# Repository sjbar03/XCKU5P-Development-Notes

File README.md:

# XCKU5P Development Notes

A repository of all my notes as I learn PCB Design, Xilinx UltraScale+ FPGA, and Vivado.

Huge thanks to the creator of [this repository](https://github.com/tommythorn/AliExpressXCKU5P) for compiling all of the relevant technical info on this board!

Table of Contents
>    [1. VGA](./vga.md)
> 
>    [2. HDMI](./hdmi.md)
> 
>    [3. Protocols](./protocols.md)
> 
>    [4. PCB](./pcb.md)

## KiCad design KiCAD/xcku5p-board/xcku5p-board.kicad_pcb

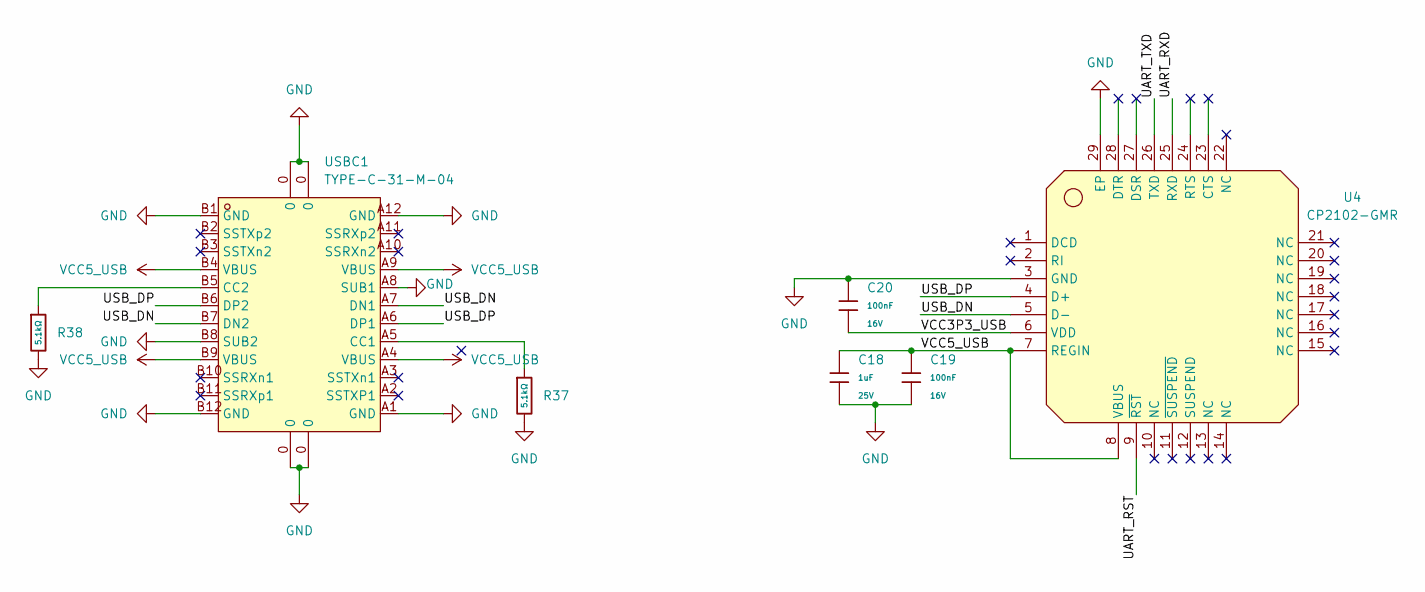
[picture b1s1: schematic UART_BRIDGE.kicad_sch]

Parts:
C18: 1uF; C_0402; Voltage Rated 25V; Tolerance ±10%; Part CL05A105KA5NQNC; LCSC C52923
C19, C20: 100nF; C_0402; Voltage Rated 16V; Tolerance ±10%; Part CL05B104KO5NNNC; LCSC C1525
R37, R38: 5.1kΩ; R_0402; Overload Voltage (Max) 50V; Tolerance ±1%; Part 0402WGF5101TCE; LCSC C25905
U4: CP2102-GMR; WQFN-28_L5.0-W5.0-P0.50-BL-EP3.2; LCSC Part C6568
USBC1: TYPE-C-31-M-04; USB-C-SMD_TYPE-C-USB-20; LCSC Part C129018

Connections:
/UART_BRIDGE/UART_RST: U4.9 (~RST)
/UART_BRIDGE/UART_RXD: U4.25 (RXD)
/UART_BRIDGE/UART_TXD: U4.26 (TXD)
/UART_BRIDGE/USB_DN: U4.5 (D-), USBC1.A7 (DN1), USBC1.B7 (DN2)
/UART_BRIDGE/USB_DP: U4.4 (D+), USBC1.A6 (DP1), USBC1.B6 (DP2)
/UART_BRIDGE/VCC3P3_USB: C20.2, U4.6 (VDD)
GND: C18.2, C19.2, C20.1, R37.2, R38.2, U4.3 (GND), U4.29 (EP), USBC1.0, USBC1.A1 (GND), USBC1.A8 (SUB1), USBC1.A12 (GND), USBC1.B1 (GND), USBC1.B8 (SUB2), USBC1.B12 (GND); also elsewhere on the board
unnamed: R37.1, USBC1.A5 (CC1)
unnamed: R38.1, USBC1.B5 (CC2)
VCC5_USB: C18.1, C19.1, U4.7 (REGIN), U4.8 (VBUS), USBC1.A4 (VBUS), USBC1.A9 (VBUS), USBC1.B4 (VBUS), USBC1.B9 (VBUS)

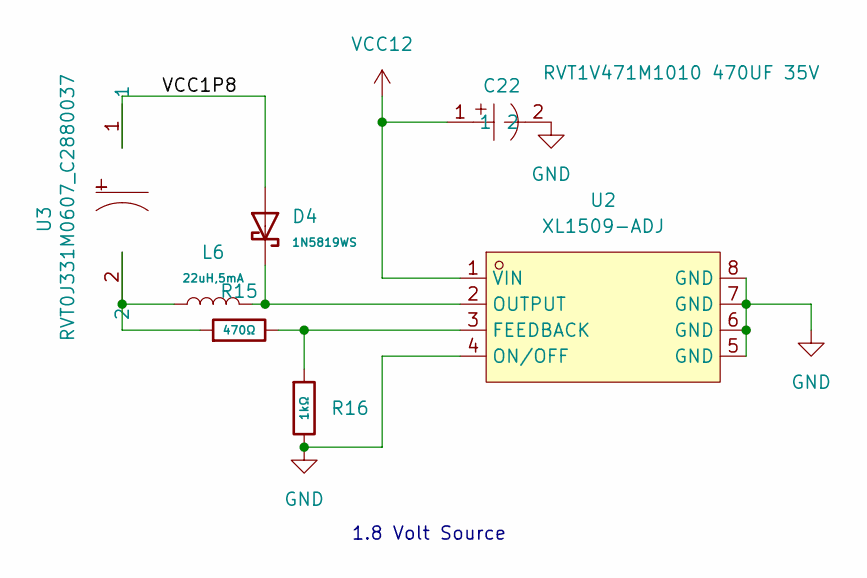
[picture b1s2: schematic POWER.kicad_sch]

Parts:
C22: RVT1V471M1010 470UF 35V; CAP-SMD_BD10.0-L10.3-W10.3-FD; LCSC Part C976030
D4: 1N5819WS; D_SOD-323; Forward Voltage (Vf@If) 600mV@1A; Reverse Voltage (Vr) 40V; Part 1N5819WS; LCSC C191023
L6: 22uH,5mA; L_0805; Tolerance ±10%; Part SDFL2012T220KTF; LCSC C32375
R15: 470Ω; R_0402; Overload Voltage (Max) 50V; Tolerance ±1%; Part 0402WGF4700TCE; LCSC C25117
R16: 1kΩ; R_0402; Overload Voltage (Max) 50V; Tolerance ±1%; Part 0402WGF1001TCE; LCSC C11702
U2: XL1509-ADJ; SOIC-8_L5.0-W4.0-P1.27-LS6.0-BL; LCSC Part C2681227
U3: RVT0J331M0607_C2880037; CAP-SMD_BD6.3-L6.6-W6.6-LS7.2-R-RD-1; LCSC Part C2880037

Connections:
/POWER/VCC1P8: D4.2, U3.1
GND: C22.2, R16.2, U2.4 (ON/OFF), U2.5 (GND), U2.6 (GND), U2.7 (GND), U2.8 (GND); also elsewhere on the board
unnamed: L6.1, R15.1, U3.2
unnamed: R15.2, R16.1, U2.3 (FEEDBACK)
unnamed: D4.1, L6.2, U2.2 (OUTPUT)
VCC12: C22.1, U2.1 (VIN)

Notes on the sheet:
1.8 Volt Source

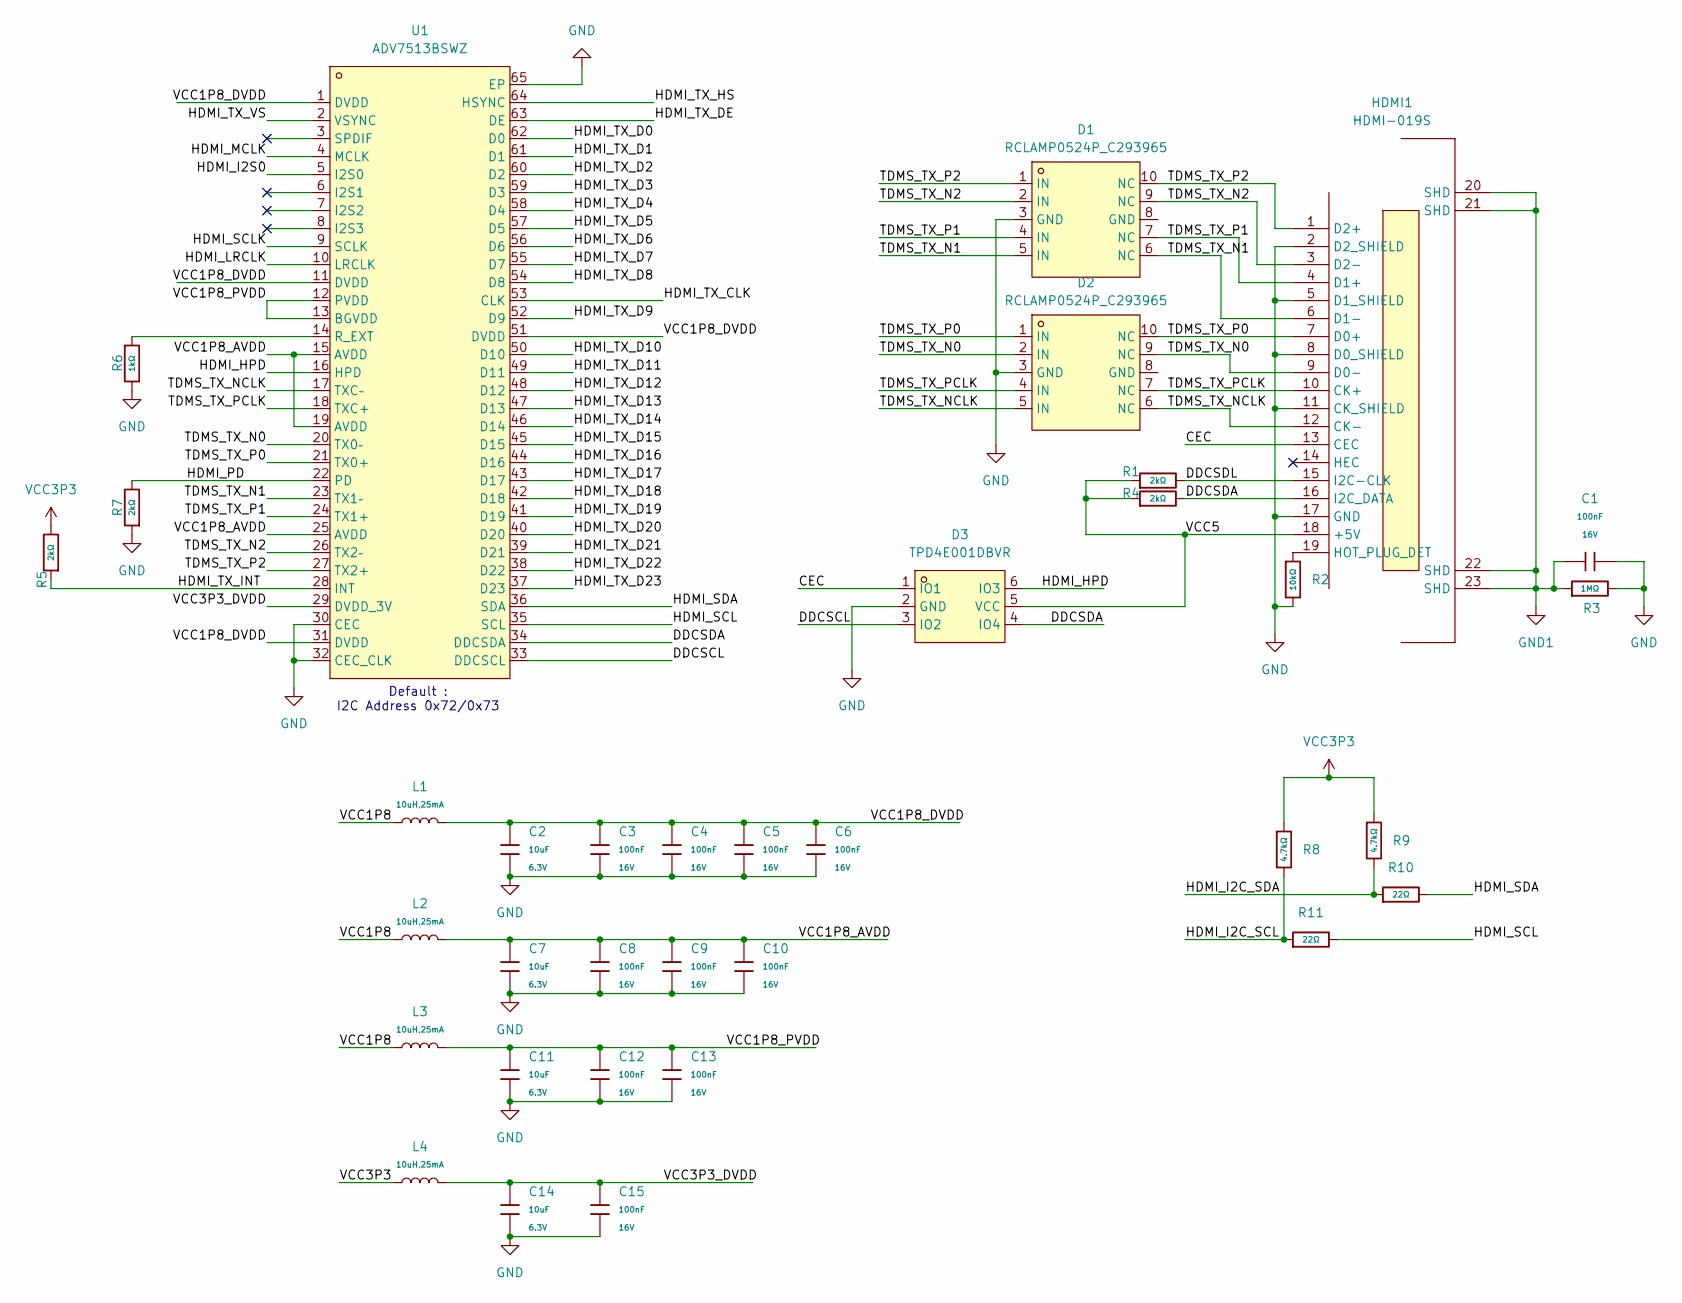
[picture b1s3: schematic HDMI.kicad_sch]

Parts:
C1, C3, C4, C5, C6, C8, C9, C10, C12, C13, C15: 100nF; C_0402; Voltage Rated 16V; Tolerance ±10%; Part CL05B104KO5NNNC; LCSC C1525
C2, C7, C11, C14: 10uF; C_0402; Voltage Rated 6.3V; Tolerance ±20%; Part CL05A106MQ5NUNC; LCSC C15525
D1, D2: RCLAMP0524P_C293965; DFN2510-10_L2.5-W1.0-P0.50-BL; LCSC Part C293965
D3: TPD4E001DBVR; SOT-23-6_L2.9-W1.6-P0.95-LS2.8-BL; LCSC Part C465736
HDMI1: HDMI-019S; HDMI-SMD_HDMI-019S; LCSC Part C111617
L1, L2, L3, L4: 10uH,25mA; L_1206; Tolerance ±10%; Part CMI321609X100KT; LCSC C1051
R1, R4, R5, R7: 2kΩ; R_0402; Overload Voltage (Max) 50V; Tolerance ±1%; Part 0402WGF2001TCE; LCSC C4109
R2: 10kΩ; R_0402; Overload Voltage (Max) 50V; Tolerance ±1%; Part 0402WGF1002TCE; LCSC C25744
R3: 1MΩ; R_0402; Overload Voltage (Max) 50V; Tolerance ±1%; Part 0402WGF1004TCE; LCSC C26083
R6: 1kΩ; R_0402; Overload Voltage (Max) 50V; Tolerance ±1%; Part 0402WGF1001TCE; LCSC C11702
R8, R9: 4.7kΩ; R_0402; Overload Voltage (Max) 50V; Tolerance ±1%; Part 0402WGF4701TCE; LCSC C25900
R10, R11: 22Ω; R_0402; Overload Voltage (Max) 50V; Tolerance ±1%; Part 0402WGF220JTCE; LCSC C25092
U1: ADV7513BSWZ; LQFP-64_L10.0-W10.0-P0.50-LS12.0-BL-EP5.3; LCSC Part C408901

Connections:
/HDMI/CEC: D3.1 (IO1), HDMI1.13 (CEC)
/HDMI/DDCSCL: D3.3 (IO2), U1.33 (DDCSCL)
/HDMI/DDCSDA: D3.4 (IO4), HDMI1.16 (I2C_DATA), R4.2, U1.34 (DDCSDA)
/HDMI/DDCSDL: HDMI1.15 (I2C-CLK), R1.2
/HDMI/HDMI_HPD: D3.6 (IO3), U1.16 (HPD)
/HDMI/HDMI_I2C_SCL: R8.2, R11.1
/HDMI/HDMI_I2C_SDA: R9.2, R10.1
/HDMI/HDMI_I2S0: U1.5 (I2S0)
/HDMI/HDMI_LRCLK: U1.10 (LRCLK)
/HDMI/HDMI_MCLK: U1.4 (MCLK)
/HDMI/HDMI_PD: R7.2, U1.22 (PD)
/HDMI/HDMI_SCL: R11.2, U1.35 (SCL)
/HDMI/HDMI_SCLK: U1.9 (SCLK)
/HDMI/HDMI_SDA: R10.2, U1.36 (SDA)
/HDMI/HDMI_TX_CLK: U1.53 (CLK)
/HDMI/HDMI_TX_D0: U1.62 (D0)
/HDMI/HDMI_TX_D1: U1.61 (D1)
/HDMI/HDMI_TX_D2: U1.60 (D2)
/HDMI/HDMI_TX_D3: U1.59 (D3)
/HDMI/HDMI_TX_D4: U1.58 (D4)
/HDMI/HDMI_TX_D5: U1.57 (D5)
/HDMI/HDMI_TX_D6: U1.56 (D6)
/HDMI/HDMI_TX_D7: U1.55 (D7)
/HDMI/HDMI_TX_D8: U1.54 (D8)
/HDMI/HDMI_TX_D9: U1.52 (D9)
/HDMI/HDMI_TX_D10: U1.50 (D10)
/HDMI/HDMI_TX_D11: U1.49 (D11)
/HDMI/HDMI_TX_D12: U1.48 (D12)
/HDMI/HDMI_TX_D13: U1.47 (D13)
/HDMI/HDMI_TX_D14: U1.46 (D14)
/HDMI/HDMI_TX_D15: U1.45 (D15)
/HDMI/HDMI_TX_D16: U1.44 (D16)
/HDMI/HDMI_TX_D17: U1.43 (D17)
/HDMI/HDMI_TX_D18: U1.42 (D18)
/HDMI/HDMI_TX_D19: U1.41 (D19)
/HDMI/HDMI_TX_D20: U1.40 (D20)
/HDMI/HDMI_TX_D21: U1.39 (D21)
/HDMI/HDMI_TX_D22: U1.38 (D22)
/HDMI/HDMI_TX_D23: U1.37 (D23)
/HDMI/HDMI_TX_DE: U1.63 (DE)
/HDMI/HDMI_TX_HS: U1.64 (HSYNC)
/HDMI/HDMI_TX_INT: R5.1, U1.28 (INT)
/HDMI/HDMI_TX_VS: U1.2 (VSYNC)
/HDMI/TDMS_TX_N0: D2.2 (IN), D2.9 (NC), HDMI1.9 (D0-), U1.20 (TX0–)
/HDMI/TDMS_TX_N1: D1.5 (IN), D1.6 (NC), HDMI1.6 (D1-), U1.23 (TX1–)
/HDMI/TDMS_TX_N2: D1.2 (IN), D1.9 (NC), HDMI1.3 (D2-), U1.26 (TX2–)
/HDMI/TDMS_TX_NCLK: D2.5 (IN), D2.6 (NC), HDMI1.12 (CK-), U1.17 (TXC–)
/HDMI/TDMS_TX_P0: D2.1 (IN), D2.10 (NC), HDMI1.7 (D0+), U1.21 (TX0+)
/HDMI/TDMS_TX_P1: D1.4 (IN), D1.7 (NC), HDMI1.4 (D1+), U1.24 (TX1+)
/HDMI/TDMS_TX_P2: D1.1 (IN), D1.10 (NC), HDMI1.1 (D2+), U1.27 (TX2+)
/HDMI/TDMS_TX_PCLK: D2.4 (IN), D2.7 (NC), HDMI1.10 (CK+), U1.18 (TXC+)
/HDMI/VCC1P8: L1.1, L2.1, L3.1
/HDMI/VCC1P8_AVDD: C7.1, C8.2, C9.2, C10.2, L2.2, U1.15 (AVDD), U1.19 (AVDD), U1.25 (AVDD)
/HDMI/VCC1P8_DVDD: C2.1, C3.2, C4.2, C5.2, C6.2, L1.2, U1.1 (DVDD), U1.11 (DVDD), U1.31 (DVDD), U1.51 (DVDD)
/HDMI/VCC1P8_PVDD: C11.1, C12.2, C13.2, L3.2, U1.12 (PVDD), U1.13 (BGVDD)
/HDMI/VCC3P3_DVDD: C14.1, C15.2, L4.2, U1.29 (DVDD_3V)
/HDMI/VCC5: D3.5 (VCC), HDMI1.18 (+5V), R1.1, R4.1
GND: C1.2, C2.2, C3.1, C4.1, C5.1, C6.1, C7.2, C8.1, C9.1, C10.1, C11.2, C12.1, C13.1, C14.2, C15.1, D1.3 (GND), D2.3 (GND), D3.2 (GND), HDMI1.2 (D2_SHIELD), HDMI1.5 (D1_SHIELD), HDMI1.8 (D0_SHIELD), HDMI1.11 (CK_SHIELD), HDMI1.17 (GND), R2.2, R3.2, R6.2, R7.1, U1.30 (CEC), U1.32 (CEC_CLK), U1.65 (EP); also elsewhere on the board
GND1: C1.1, HDMI1.20 (SHD), HDMI1.21 (SHD), HDMI1.22 (SHD), HDMI1.23 (SHD), R3.1
unnamed: HDMI1.19 (HOT_PLUG_DET), R2.1
unnamed: R6.1, U1.14 (R_EXT)
VCC3P3: L4.1, R5.2, R8.1, R9.1; also elsewhere on the board

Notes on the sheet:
Default : I2C Address 0x72/0x73

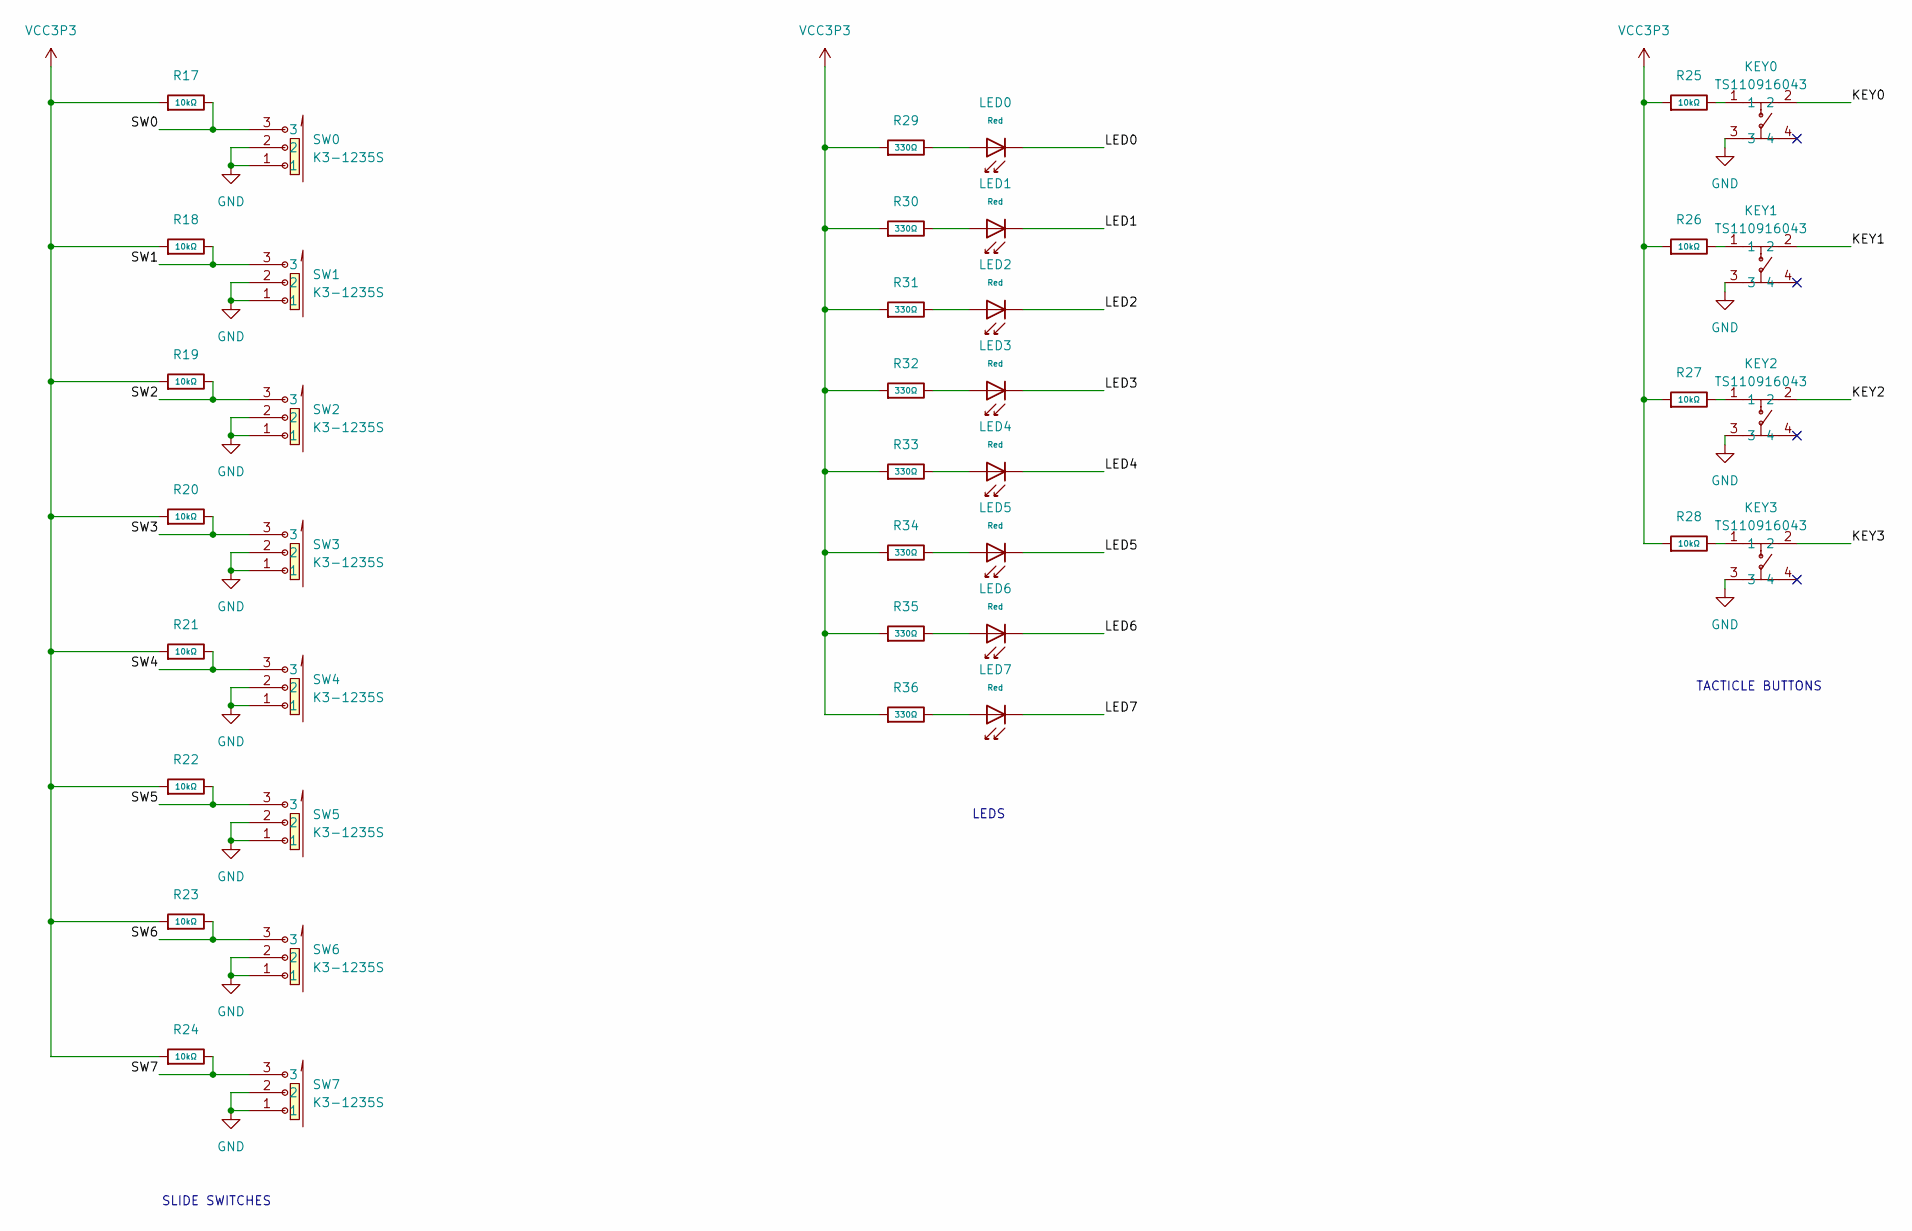
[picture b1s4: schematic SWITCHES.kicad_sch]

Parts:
KEY0, KEY1, KEY2, KEY3: TS110916043; SW-SMD_4P-L4.5-W4.5-P3.00-LS7.5; LCSC Part C22375348
LED0, LED1, LED2, LED3, LED4, LED5, LED6, LED7: Red; D_0603; Part KT-0603R; LCSC C2286
R17, R18, R19, R20, R21, R22, R23, R24, R25, R26, R27, R28: 10kΩ; R_0402; Overload Voltage (Max) 50V; Tolerance ±1%; Part 0402WGF1002TCE; LCSC C25744
R29, R30, R31, R32, R33, R34, R35, R36: 330Ω; R_0402; Overload Voltage (Max) 50V; Tolerance ±1%; Part 0402WGF3300TCE; LCSC C25104
SW0, SW1, SW2, SW3, SW4, SW5, SW6, SW7: K3-1235S; SW-SMD_K3-1235S-K1; LCSC Part C92660

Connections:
/SWITCHES/KEY0: KEY0.2
/SWITCHES/KEY1: KEY1.2
/SWITCHES/KEY2: KEY2.2
/SWITCHES/KEY3: KEY3.2
/SWITCHES/LED0: LED0.1
/SWITCHES/LED1: LED1.1
/SWITCHES/LED2: LED2.1
/SWITCHES/LED3: LED3.1
/SWITCHES/LED4: LED4.1
/SWITCHES/LED5: LED5.1
/SWITCHES/LED6: LED6.1
/SWITCHES/LED7: LED7.1
/SWITCHES/SW0: R17.2, SW0.3
/SWITCHES/SW1: R18.2, SW1.3
/SWITCHES/SW2: R19.2, SW2.3
/SWITCHES/SW3: R20.2, SW3.3
/SWITCHES/SW4: R21.2, SW4.3
/SWITCHES/SW5: R22.2, SW5.3
/SWITCHES/SW6: R23.2, SW6.3
/SWITCHES/SW7: R24.2, SW7.3
GND: KEY0.3, KEY1.3, KEY2.3, KEY3.3, SW0.1, SW0.2, SW1.1, SW1.2, SW2.1, SW2.2, SW3.1, SW3.2, SW4.1, SW4.2, SW5.1, SW5.2, SW6.1, SW6.2, SW7.1, SW7.2; also elsewhere on the board
unnamed: KEY0.1, R25.2
unnamed: KEY1.1, R26.2
unnamed: KEY2.1, R27.2
unnamed: KEY3.1, R28.2
unnamed: LED0.2, R29.2
unnamed: LED1.2, R30.2
unnamed: LED2.2, R31.2
unnamed: LED3.2, R32.2
unnamed: LED4.2, R33.2
unnamed: LED5.2, R34.2
unnamed: LED6.2, R35.2
unnamed: LED7.2, R36.2
VCC3P3: R17.1, R18.1, R19.1, R20.1, R21.1, R22.1, R23.1, R24.1, R25.1, R26.1, R27.1, R28.1, R29.1, R30.1, R31.1, R32.1, R33.1, R34.1, R35.1, R36.1; also elsewhere on the board

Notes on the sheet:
LEDS
TACTICLE BUTTONS
SLIDE SWITCHES

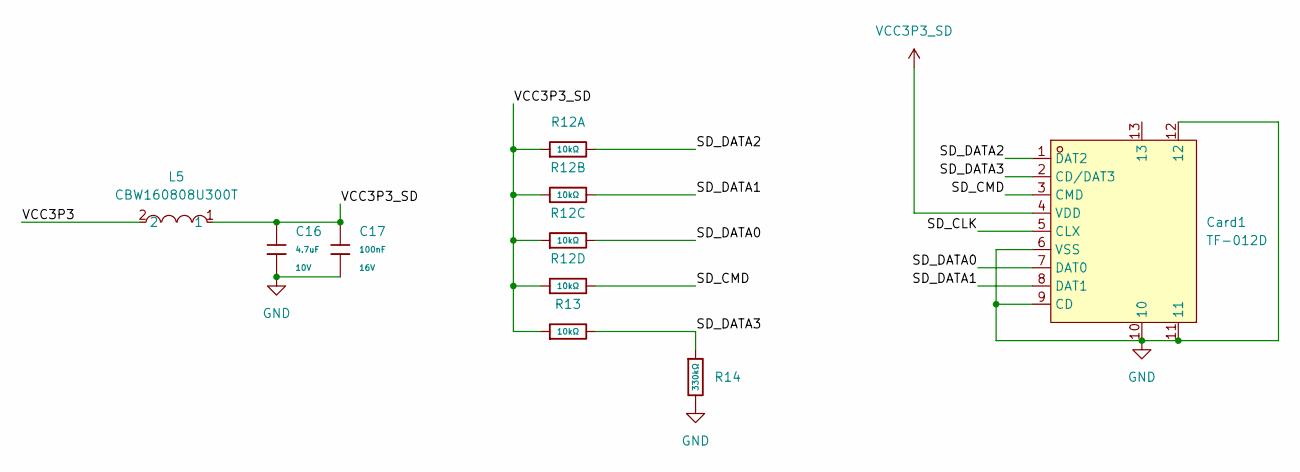
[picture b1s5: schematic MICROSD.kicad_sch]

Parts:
C16: 4.7uF; C_0402; Voltage Rated 10V; Tolerance ±20%; Part CL05A475MP5NRNC; LCSC C23733
C17: 100nF; C_0402; Voltage Rated 16V; Tolerance ±10%; Part CL05B104KO5NNNC; LCSC C1525
Card1: TF-012D; TF-SMD_TF-012; LCSC Part C2874207
L5: CBW160808U300T; L0603; LCSC Part C139178
R12: 10kΩ; R_0402x4; Tolerance ±5%; Part 4D02WGJ0103TCE; LCSC C25725
R13: 10kΩ; R_0402; Overload Voltage (Max) 50V; Tolerance ±1%; Part 0402WGF1002TCE; LCSC C25744
R14: 330kΩ; R_0402; Overload Voltage (Max) 50V; Tolerance ±1%; Part 0402WGF3303TCE; LCSC C25778

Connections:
/MICROSD/SD_CLK: Card1.5 (CLX)
/MICROSD/SD_CMD: Card1.3 (CMD), R12.5
/MICROSD/SD_DATA0: Card1.7 (DAT0), R12.6
/MICROSD/SD_DATA1: Card1.8 (DAT1), R12.7
/MICROSD/SD_DATA2: Card1.1 (DAT2), R12.8
/MICROSD/SD_DATA3: Card1.2 (CD/DAT3), R13.2, R14.1
/MICROSD/VCC3P3: L5.2
GND: C16.2, C17.2, Card1.6 (VSS), Card1.9 (CD), Card1.10, Card1.11, Card1.12, R14.2; also elsewhere on the board
VCC3P3_SD: C16.1, C17.1, Card1.4 (VDD), L5.1, R12.1, R12.2, R12.3, R12.4, R13.1

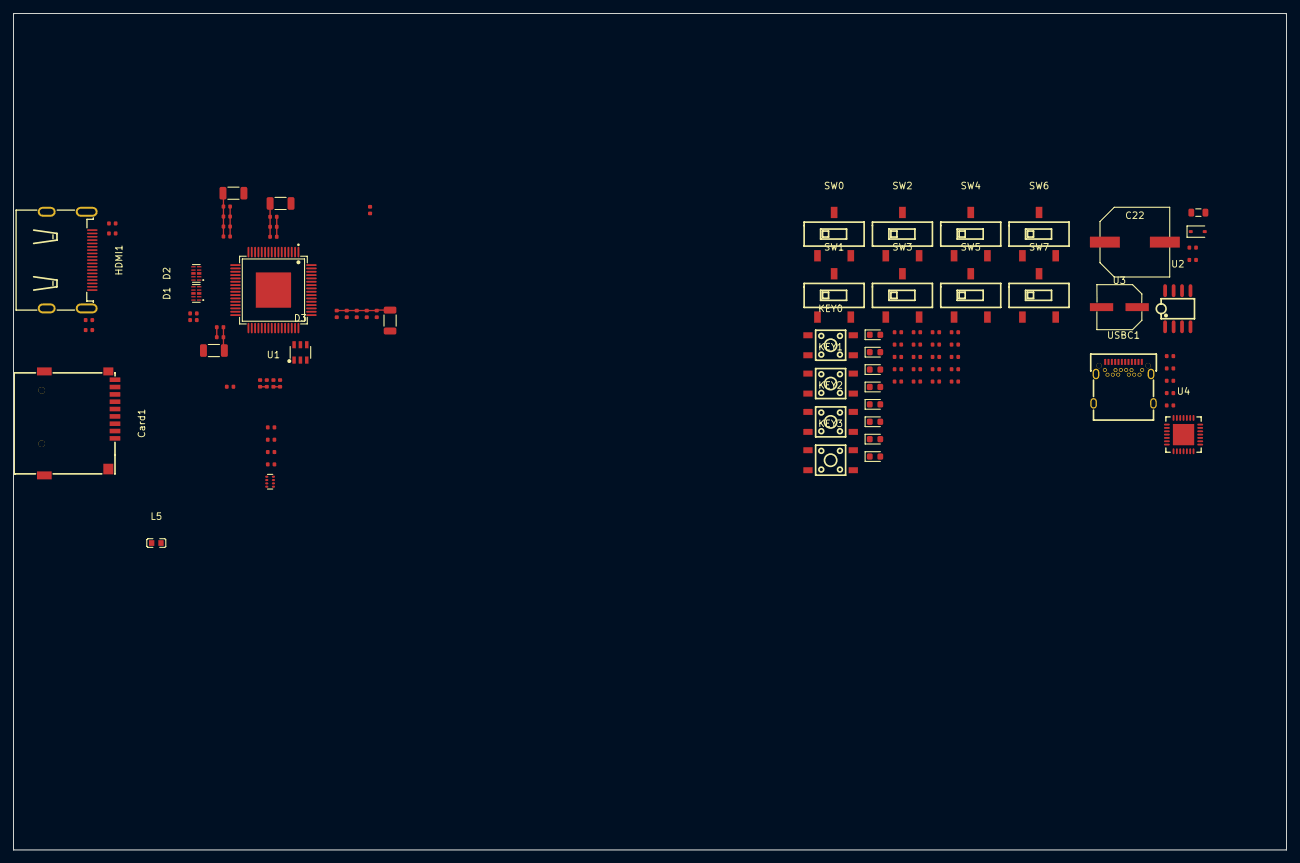
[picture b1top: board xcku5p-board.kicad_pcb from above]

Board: 2 copper layers, 191.0 x 125.5 mm, 96 parts (0 on the bottom side), 67 nets.

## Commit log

2026-03-10 Initial commit. Add documentation and notes for HDMI/LVDS
2026-03-10 Add PDF for example hdmi sub system.
2026-03-10 Work on hdmi
2026-03-10 Start VGA research.
2026-03-12 Add pcb.md & Altium docs! - VGA circuit rev 1 done - VGA notes expanded
2026-03-12 Fix math formatting in vga.md
2026-03-12 Add .gitattributes for Markdown file recognition
    Configure .gitattributes to ensure Markdown files are recognized correctly and suppress misdetections.
2026-03-12 Add README
2026-03-12 Fix formatting in README.md Table of Contents
2026-03-13 Fix typo
2026-03-17 Add notes on clocking and MMCM
2026-03-17 Add RTL for working blinking LED Demo! - This demo blinks two of the onboard LEDs at two different speeds - Sources the input clock from the onboard crystal oscillator and generates a 200MHz clock us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
2026-03-17 Switch to real pins for VGA
2026-03-20 Continue developing PCB!
2026-03-20 Add Switches and Keys to the PCB. Add microsd card slot.
2026-03-21 Cleaning up pcb design for JLCPCB! Almost ready to fab.
2026-03-21 Finish revision one of PCB! Reconsidering paying for a custom PCB and instead going for the other ebay board...
2026-03-25 Start working on HDMI circuit based on DE10
2026-03-26 Switching to KiCAD, and going for HDMI + Ethernet
2026-03-26 Add SD card circuit
2026-03-27 Add power circuit, switches, UART bridge
